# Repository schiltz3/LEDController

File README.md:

# Power Distribution Board Screenshots
Schematic:
[LEDControllerPDB/Outputs/LED Power Distribution Board sch.pdf](https://github.com/schiltz3/LEDController/blob/ab43750f7913fe42482215626bbdc119c35f3c25/LEDControllerPDB/Outputs/LED%20Power%20Distribution%20Board%20sch.pdf)
Front:

Back:

All:

# Controll Board
Schematic:
[LEDControllerBrain/Outputs/LED Control Board sch.pdf](https://github.com/schiltz3/LEDController/blob/master/LEDControllerBrain/Outputs/LED%20Control%20Board%20sch.pdf)
Front:

Back:

All:

# Assemmbly

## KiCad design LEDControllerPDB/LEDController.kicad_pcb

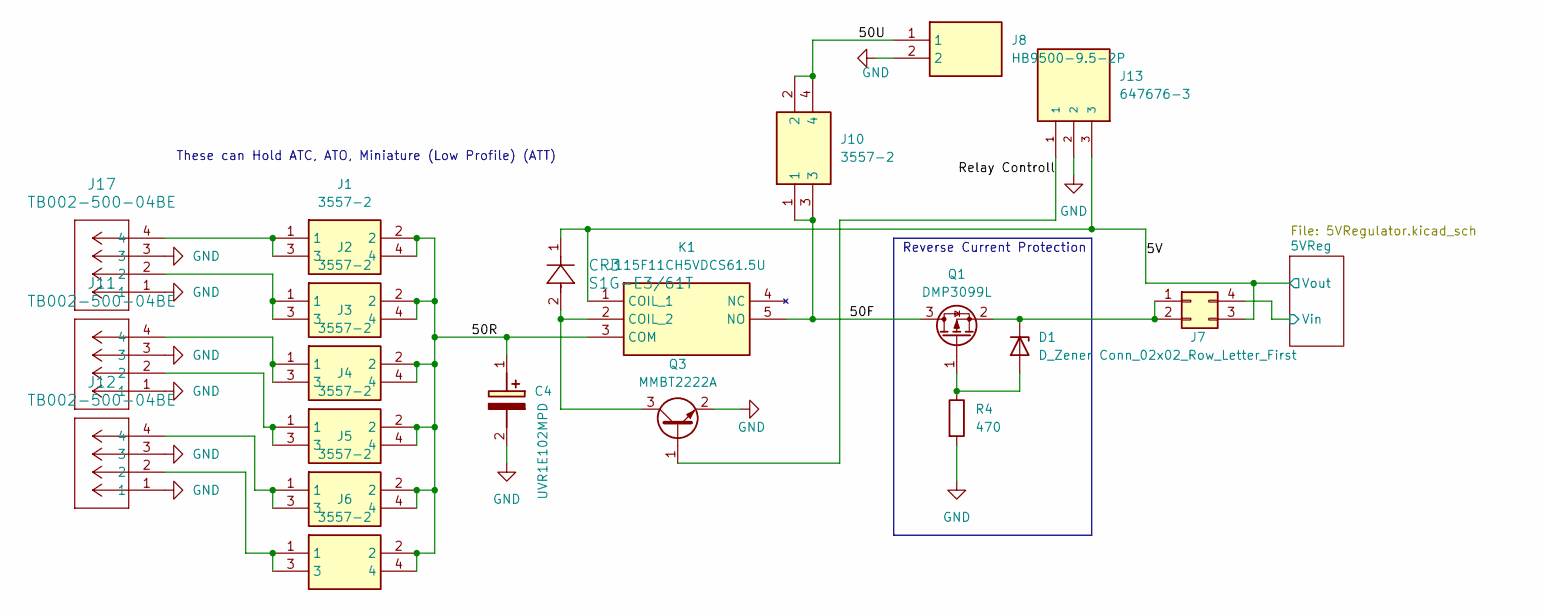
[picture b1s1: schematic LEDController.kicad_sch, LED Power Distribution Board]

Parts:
C4: UVR1E102MPD; CAPPRD500W60D1025H2200; Manufacturer_Part_Number UVR1E102MPD; Mouser Part Number 647-UVR1E102MPD
CR3: S1G-E3/61T; DIODE_DO214AC
D1: D_Zener; D_SOD-123
J1, J2, J3, J4, J5, J6, J10: 3557-2; Mouser Part Number 534-3557-2
J7: Conn_02x02_Row_Letter_First; PinHeader_2x02_P2.54mm_Vertical
J8: HB9500-9.5-2P; SHDR2W140P0X950_1X2_2055X1800X1440P; Manufacturer_Part_Number HB9500-9.5-2P
J11, J12, J17: TB002-500-04BE; CONN4_TB002-500_787x299_CUD
J13: 647676-3; TE_647676-3; PARTREV R
K1: J115F11CH5VDCS61.5U; J115F11CH5VDCS615U; Manufacturer_Part_Number J115F11CH5VDCS61.5U
Q1: DMP3099L; SOT-23-3
Q3: MMBT2222A; SOT-23
R4: 470; R_0603_1608Metric_Pad0.98x0.95mm_HandSolder

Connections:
/5V: CR3.1, J7.3, J13.3, K1.1 (COIL_1); also elsewhere on the board
/5VReg/Vin: J7.4; also elsewhere on the board
/50F: J10.1, J10.3, K1.5 (NO), Q1.3 (D)
/50R: C4.1 (+), J1.2, J1.4, J2.2, J2.4, J3.2, J3.4, J4.2, J4.4, J5.2, J5.4, J6.2, J6.4, K1.3 (COM)
/50U: J8.1, J10.2, J10.4
/Relay Controll: J13.1, Q3.1 (B)
GND: C4.2 (-), J8.2, J11.1, J11.3, J12.1, J12.3, J13.2, J17.1, J17.3, Q3.2 (E), R4.2; also elsewhere on the board
unnamed: D1.2 (A), Q1.1 (G), R4.1
unnamed: D1.1 (K), J7.1, J7.2, Q1.2 (S)
unnamed: J1.1, J1.3, J17.4
unnamed: J4.1, J4.3, J11.2
unnamed: J3.1, J3.3, J11.4
unnamed: J6.1, J6.3, J12.2
unnamed: J5.1, J5.3, J12.4
unnamed: J2.1, J2.3, J17.2
unnamed: CR3.2, K1.2 (COIL_2), Q3.3 (C)

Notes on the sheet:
Reverse Current Protection
These can Hold ATC, ATO, Miniature (Low Profile) (ATT)

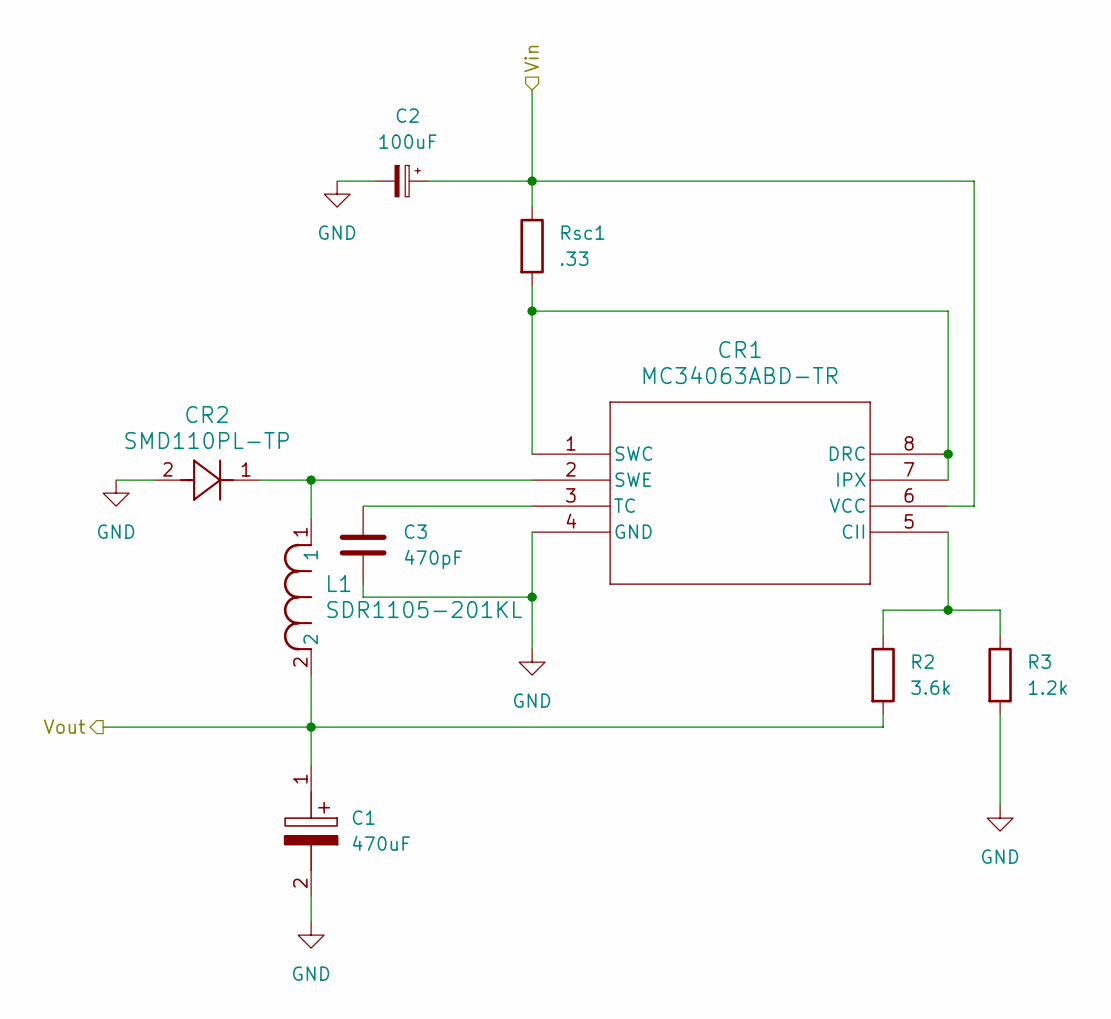
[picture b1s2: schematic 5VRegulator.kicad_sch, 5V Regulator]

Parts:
C1: 470uF; CAPPRD500W60D1000H1350; Manufacturer_Part_Number ESK477M025AH1EA; Mouser Part Number 80-ESK477M025AH1EA
C2: 100uF; CP_Radial_D5.0mm_P2.50mm
C3: 470pF; C_0603_1608Metric_Pad1.08x0.95mm_HandSolder
CR1: MC34063ABD-TR; SO-8_STM
CR2: SMD110PL-TP; SOD-123FL_MCC
L1: SDR1105-201KL; IND_BOURNS_SDR1105
R2: 3.6k; R_0603_1608Metric_Pad0.98x0.95mm_HandSolder
R3: 1.2k; R_0603_1608Metric_Pad0.98x0.95mm_HandSolder
Rsc1: .33; R_0603_1608Metric_Pad0.98x0.95mm_HandSolder

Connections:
/5V: C1.1, L1.2, R2.2; also elsewhere on the board
/5VReg/Vin: C2.1, CR1.6 (VCC), Rsc1.1; also elsewhere on the board
GND: C1.2, C2.2, C3.2, CR1.4 (GND), CR2.2, R3.2; also elsewhere on the board
unnamed: CR1.5 (CII), R2.1, R3.1
unnamed: CR1.1 (SWC), CR1.7 (IPX), CR1.8 (DRC), Rsc1.2
unnamed: CR1.2 (SWE), CR2.1, L1.1
unnamed: C3.1, CR1.3 (TC)

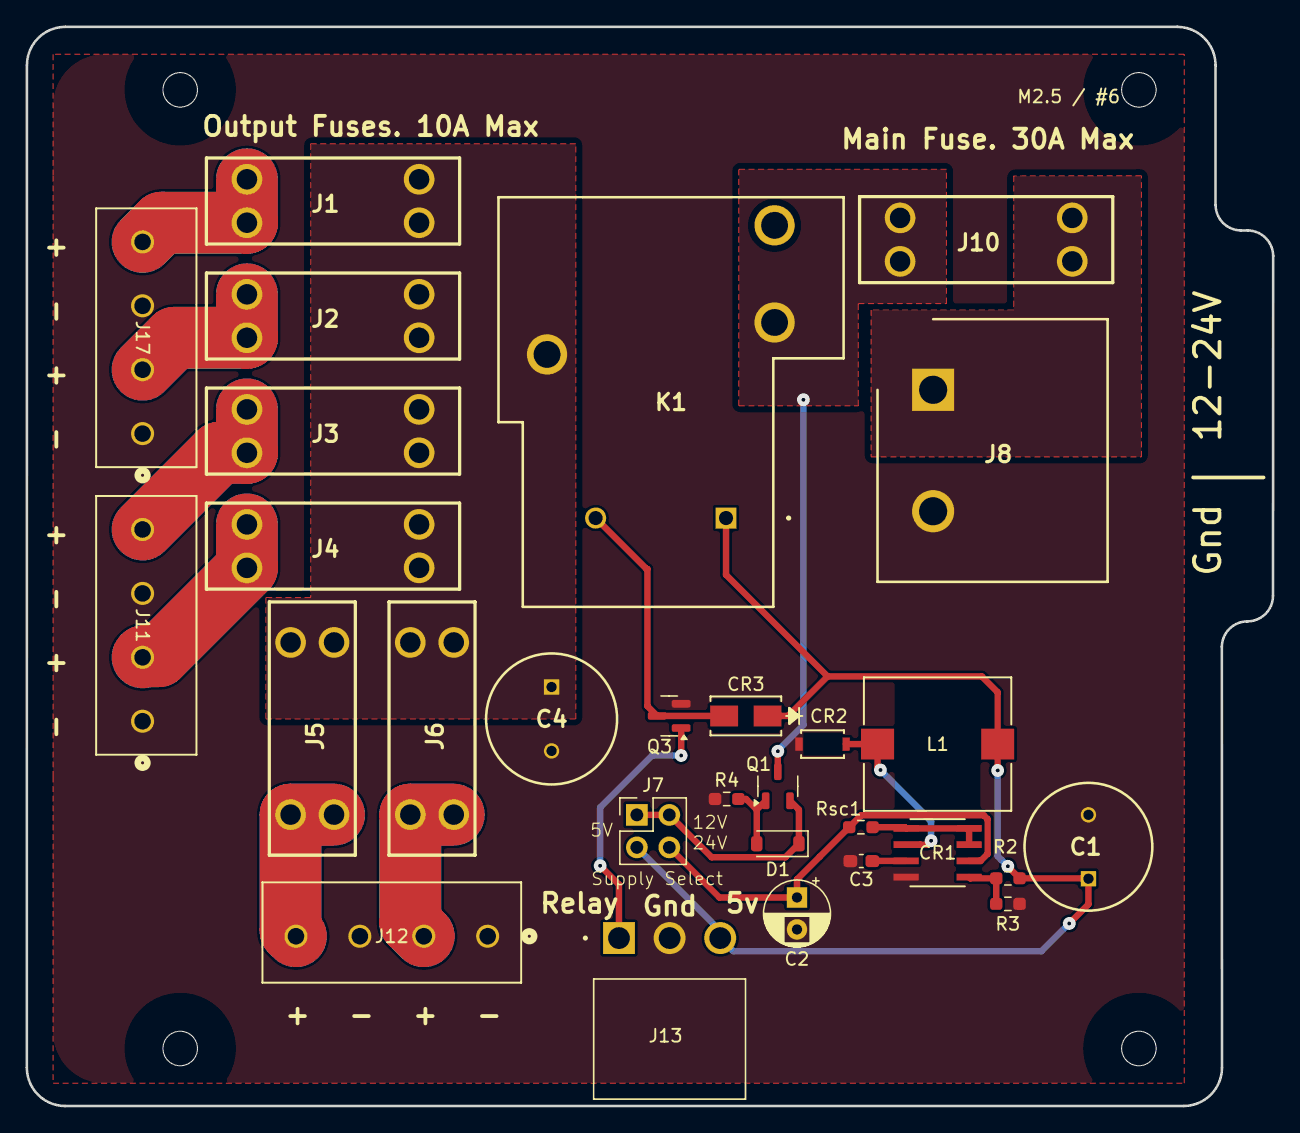
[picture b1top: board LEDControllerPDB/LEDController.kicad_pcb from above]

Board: 2 copper layers, 97.5 x 84.4 mm, 30 parts (0 on the bottom side), 20 nets.

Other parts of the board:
M2.5 / #6: MountingHole_2.7mm_M2.5

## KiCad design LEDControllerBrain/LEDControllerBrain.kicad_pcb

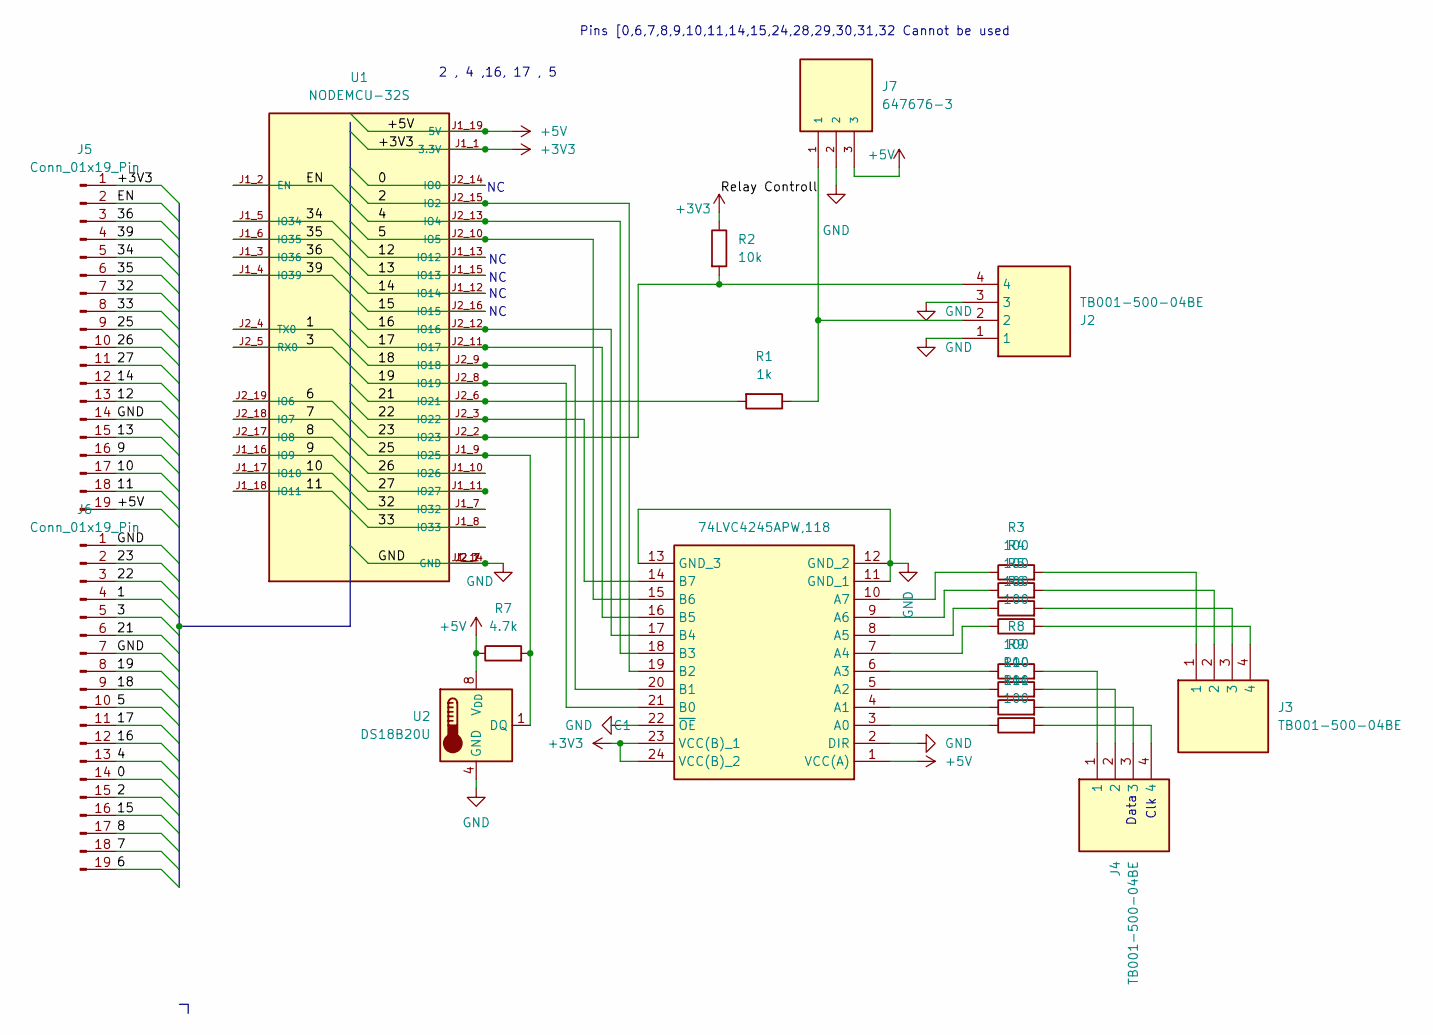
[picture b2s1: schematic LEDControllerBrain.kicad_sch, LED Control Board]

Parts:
IC1: 74LVC4245APW,118; SOP65P640X110-24N; Manufacturer_Part_Number 74LVC4245APW,118; Mouser Part Number 771-74LVC4245APW-T
J2, J3, J4: TB001-500-04BE; TB00150004BE; Manufacturer_Part_Number TB001-500-04BE
J5, J6: Conn_01x19_Pin; PinSocket_1x19_P2.54mm_Vertical
J7: 647676-3; TE_647676-3; PARTREV R
R1: 1k; R_0603_1608Metric_Pad0.98x0.95mm_HandSolder
R2: 10k; R_0603_1608Metric_Pad0.98x0.95mm_HandSolder
R3, R4, R5, R6, R8, R9, R10, R11: 100; R_0603_1608Metric_Pad0.98x0.95mm_HandSolder
R7: 4.7k; R_0603_1608Metric_Pad0.98x0.95mm_HandSolder
U1: NODEMCU-32S; MODULE_NODEMCU-32S; PARTREV V1
U2: DS18B20U; MSOP-8_3x3mm_P0.65mm

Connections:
+5V: IC1.1 (VCC(A)), J5.19, J7.3, R7.1, U1.J1_19 (5V), U2.8 (V_{DD})
/0: J6.14, U1.J2_14 (IO0)
/1: J6.4, U1.J2_4 (TX0)
/2: IC1.19 (B2), J6.15, U1.J2_15 (IO2)
/3: J6.5, U1.J2_5 (RX0)
/4: IC1.18 (B3), J6.13, U1.J2_13 (IO4)
/5: IC1.15 (B6), J6.10, U1.J2_10 (IO5)
/6: J6.19, U1.J2_19 (IO6)
/7: J6.18, U1.J2_18 (IO7)
/8: J6.17, U1.J2_17 (IO8)
/9: J5.16, U1.J1_16 (IO9)
/10: J5.17, U1.J1_17 (IO10)
/11: J5.18, U1.J1_18 (IO11)
/12: J5.13, U1.J1_13 (IO12)
/13: J5.15, U1.J1_15 (IO13)
/14: J5.12, U1.J1_12 (IO14)
/15: J6.16, U1.J2_16 (IO15)
/16: IC1.17 (B4), J6.12, U1.J2_12 (IO16)
/17: IC1.16 (B5), J6.11, U1.J2_11 (IO17)
/18: IC1.20 (B1), J6.9, U1.J2_9 (IO18)
/19: IC1.21 (B0), J6.8, U1.J2_8 (IO19)
/21: J6.6, R1.2, U1.J2_6 (IO21)
/22: IC1.14 (B7), J6.3, U1.J2_3 (IO22)
/25: J5.9, R7.2, U1.J1_9 (IO25), U2.1 (DQ)
/26: J5.10, U1.J1_10 (IO26)
/27: J5.11, U1.J1_11 (IO27)
/32: J5.7, U1.J1_7 (IO32)
/33: J5.8, U1.J1_8 (IO33)
/34: J5.5, U1.J1_5 (IO34)
/35: J5.6, U1.J1_6 (IO35)
/36: J5.3, U1.J1_3 (IO36)
/39: J5.4, U1.J1_4 (IO39)
/EN: J5.2, U1.J1_2 (EN)
/Relay Controll: J2.2, J7.1, R1.1
GND: IC1.2 (DIR), IC1.11 (GND_1), IC1.12 (GND_2), IC1.13 (GND_3), IC1.22 (~OE), J2.1, J2.3, J5.14, J6.1, J6.7, J7.2, U1.J1_14 (GND), U1.J2_1 (GND), U1.J2_7 (GND), U2.4 (GND)
unnamed: IC1.3 (A0), R11.1
unnamed: IC1.4 (A1), R10.1
unnamed: IC1.5 (A2), R9.1
unnamed: IC1.6 (A3), R8.1
unnamed: IC1.7 (A4), R6.1
unnamed: IC1.8 (A5), R5.1
unnamed: IC1.9 (A6), R4.1
unnamed: IC1.10 (A7), R3.1
unnamed: J3.1, R3.2
unnamed: J3.2, R4.2
unnamed: J3.3, R5.2
unnamed: J3.4, R6.2
unnamed: J4.1, R8.2
unnamed: J4.2, R9.2
unnamed: J4.3, R10.2
unnamed: J4.4, R11.2

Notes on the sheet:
Pins [0,6,7,8,9,10,11,14,15,24,28,29,30,31,32 Cannot be used
2 , 4 ,16, 17 , 5
Data
Clk

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
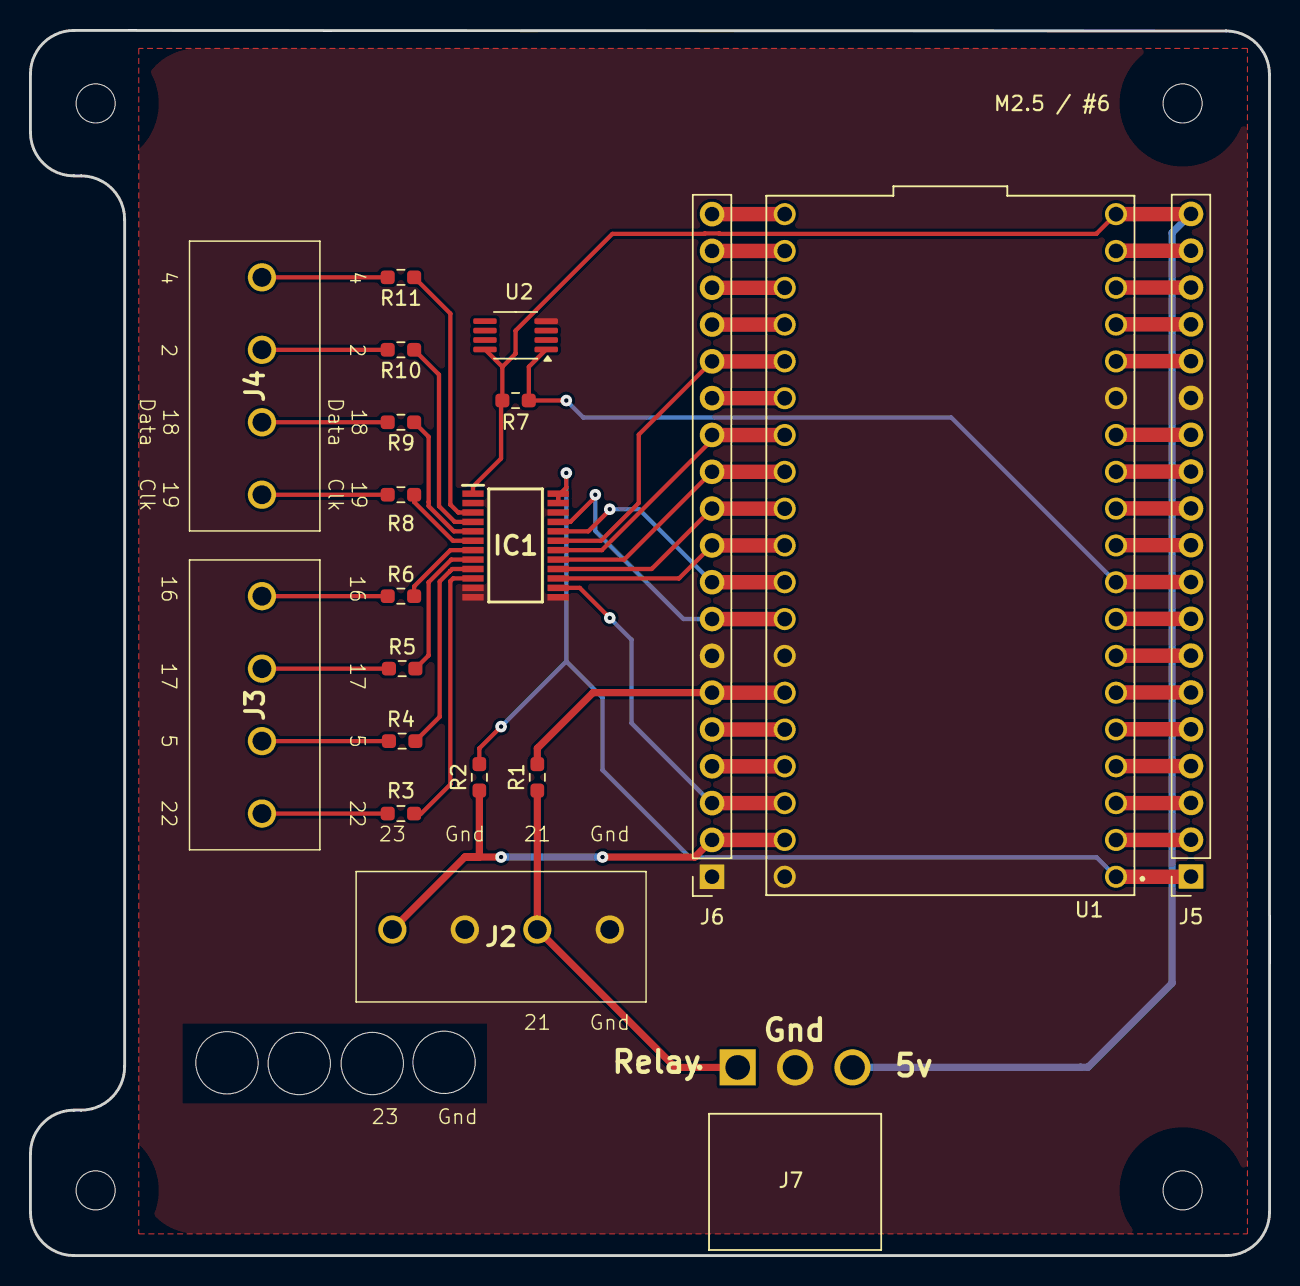
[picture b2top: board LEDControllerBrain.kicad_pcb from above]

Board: 2 copper layers, 85.5 x 84.5 mm, 21 parts (0 on the bottom side), 53 nets.

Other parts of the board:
M2.5 / #6: MountingHole_2.7mm_M2.5

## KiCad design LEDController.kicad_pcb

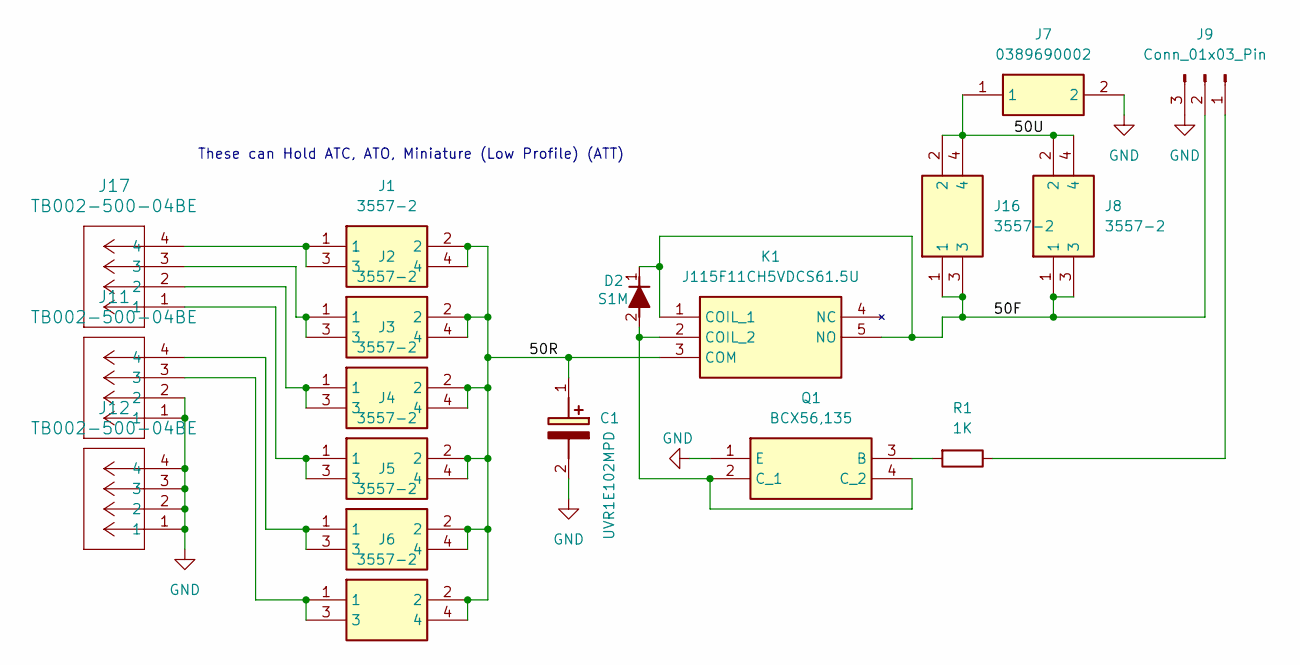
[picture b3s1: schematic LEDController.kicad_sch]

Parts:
C1: UVR1E102MPD; CAPPRD500W60D1025H2200; Manufacturer_Part_Number UVR1E102MPD; Mouser Part Number 647-UVR1E102MPD
D2: S1M; DIOM5336X240N; Manufacturer_Part_Number S1M
J1, J2, J3, J4, J5, J6, J8, J16: 3557-2; Mouser Part Number 534-3557-2
J7: 0389690002; Manufacturer_Part_Number 0389690002; Mouser Part Number N/A
J9: Conn_01x03_Pin; PinSocket_1x03_P2.54mm_Vertical
J11, J12, J17: TB002-500-04BE; CONN4_TB002-500_787x299_CUD
K1: J115F11CH5VDCS61.5U; J115F11CH5VDCS615U; Manufacturer_Part_Number J115F11CH5VDCS61.5U
Q1: BCX56,135; PBSS4360XX; Manufacturer_Part_Number BCX56,135; Mouser Part Number 771-BCX56135
R1: 1K; R_0603_1608Metric_Pad0.98x0.95mm_HandSolder

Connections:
/50F: D2.1 (K), J8.1, J8.3, J9.2, J16.1, J16.3, K1.1 (COIL_1), K1.5 (NO)
/50R: C1.1 (+), J1.2, J1.4, J2.2, J2.4, J3.2, J3.4, J4.2, J4.4, J5.2, J5.4, J6.2, J6.4, K1.3 (COM)
/50U: J7.1, J8.2, J8.4, J16.2, J16.4
GND: C1.2 (-), J7.2, J9.3, J11.1, J11.2, J12.1, J12.2, J12.3, J12.4, Q1.1 (E)
unnamed: D2.2 (A), K1.2 (COIL_2), Q1.2 (C_1), Q1.4 (C_2)
unnamed: J1.1, J1.3, J17.4
unnamed: J9.1, R1.1
unnamed: J6.1, J6.3, J11.3
unnamed: J5.1, J5.3, J11.4
unnamed: J4.1, J4.3, J17.1
unnamed: J3.1, J3.3, J17.2
unnamed: J2.1, J2.3, J17.3
unnamed: Q1.3 (B), R1.2

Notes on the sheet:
These can Hold ATC, ATO, Miniature (Low Profile) (ATT)

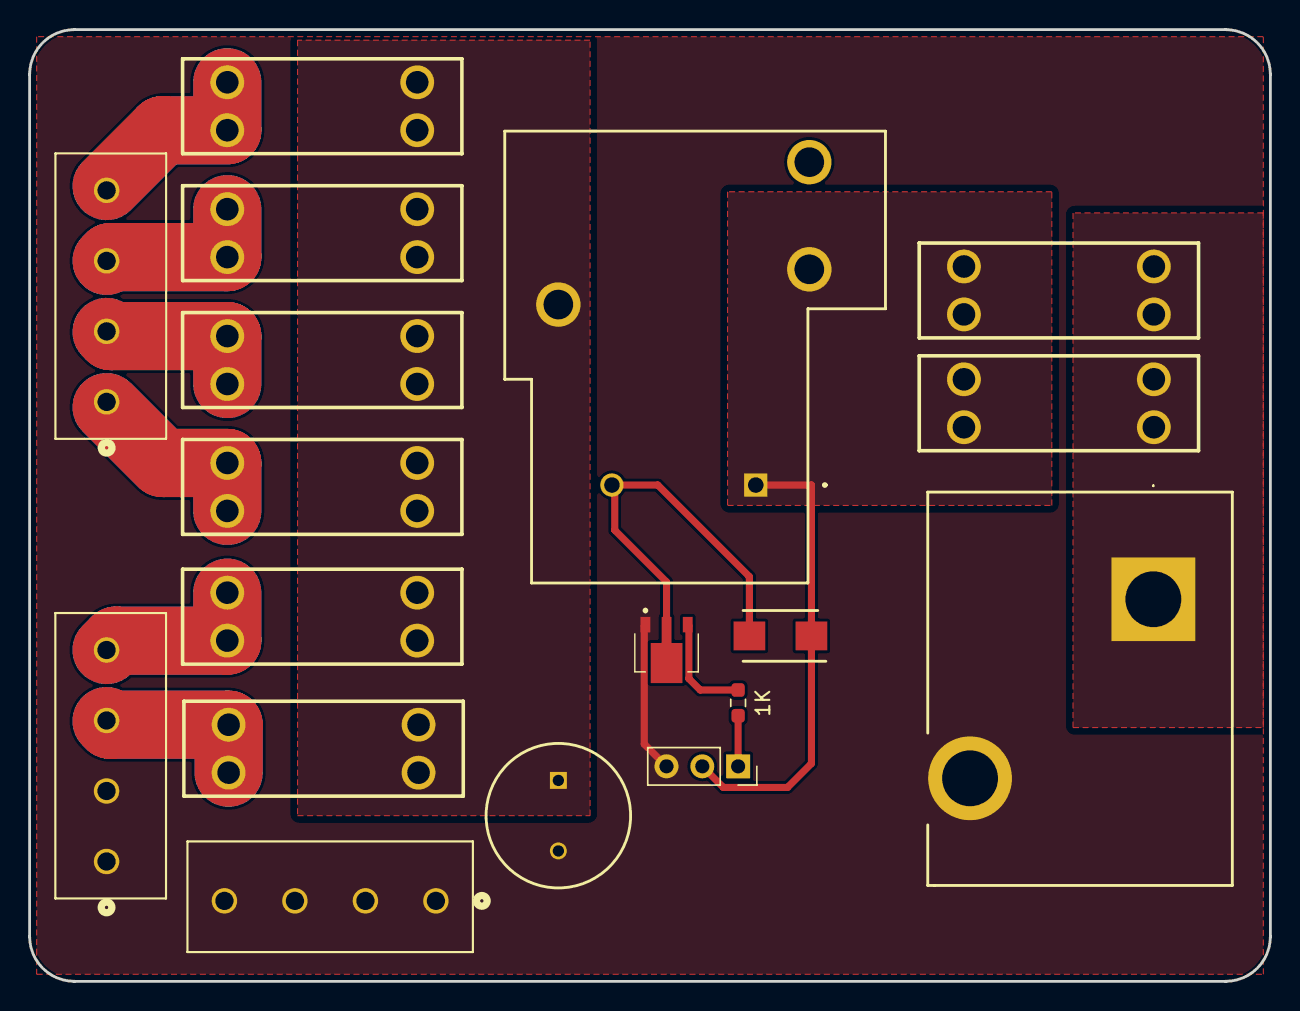
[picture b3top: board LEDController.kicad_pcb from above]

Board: 2 copper layers, 88.0 x 67.5 mm, 18 parts (0 on the bottom side), 13 nets.

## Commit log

2024-12-22 Added diode and transistor
2024-12-23 Added screw terminals
2024-12-23 updated pcb
2024-12-23 Added new high current terminal
2024-12-24 remove lock
2024-12-24 ignore lock files
2024-12-24 final schematic
2024-12-27 add footprints from laptop
2024-12-27 wip layout
2024-12-27 laptop library
2024-12-27 add schematic and footprints
2024-12-27 rename
2024-12-27 laptop footprints and sch
2024-12-27 everything from laptop
2024-12-30 Final Layout
2025-01-04 finished
2025-01-04 closed out
2025-02-01 add nodemcu
2025-04-07 fix 3d folder name
2025-04-07 Add new footprints
2025-04-07 add 24v support and reverse voltage protection
2025-04-07 rerout
2025-04-08 backups
2025-04-08 3d shapes
2025-04-08 hand solder
2025-04-09 finished pdb
2025-04-17 done
2025-04-17 resize image
2025-04-18 generate outputs
2025-04-21 add name
2025-04-22 fix regulator
2025-04-24 increase pad size
